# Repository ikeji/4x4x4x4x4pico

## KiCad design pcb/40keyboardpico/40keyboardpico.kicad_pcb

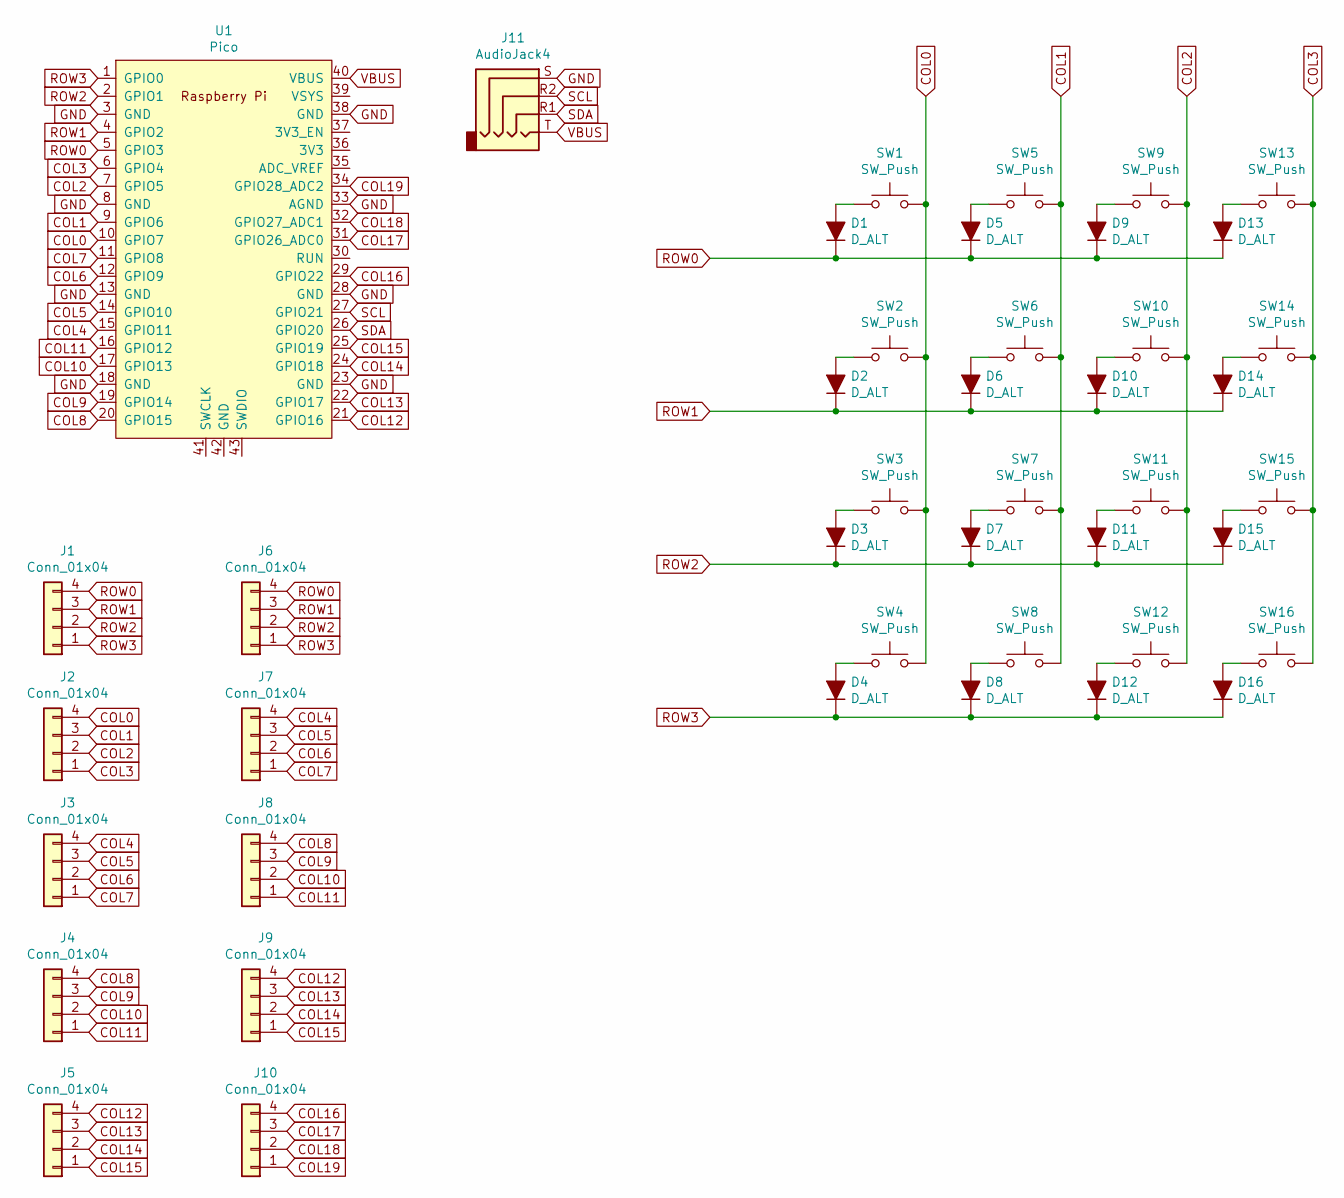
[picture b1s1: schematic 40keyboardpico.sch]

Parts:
D1, D2, D3, D4, D5, D6, D7, D8, D9, D10, D11, D12, D13, D14, D15, D16: D_ALT; D_DO-34_SOD68_P10.16mm_Horizontal
J1, J2, J3, J4, J5, J6, J7, J8, J9, J10: Conn_01x04; PinHeader_1x04_P2.54mm_Vertical
J11: AudioJack4; Jack_3.5mm_PJ320E_Horizontal
SW1, SW2, SW3, SW4, SW5, SW6, SW7, SW8, SW9, SW10, SW11, SW12, SW13, SW14, SW15, SW16: SW_Push; SW_Cherry_MX_1.00u_PCB
U1: Pico; RPi_Pico_SMD_TH

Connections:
COL0: J2.4, SW1.2, SW2.2, SW3.2, SW4.2, U1.10 (GPIO7)
COL1: J2.3, SW5.2, SW6.2, SW7.2, SW8.2, U1.9 (GPIO6)
COL2: J2.2, SW9.2, SW10.2, SW11.2, SW12.2, U1.7 (GPIO5)
COL3: J2.1, SW13.2, SW14.2, SW15.2, SW16.2, U1.6 (GPIO4)
COL4: J3.4, J7.4, U1.15 (GPIO11)
COL5: J3.3, J7.3, U1.14 (GPIO10)
COL6: J3.2, J7.2, U1.12 (GPIO9)
COL7: J3.1, J7.1, U1.11 (GPIO8)
COL8: J4.4, J8.4, U1.20 (GPIO15)
COL9: J4.3, J8.3, U1.19 (GPIO14)
COL10: J4.2, J8.2, U1.17 (GPIO13)
COL11: J4.1, J8.1, U1.16 (GPIO12)
COL12: J5.4, J9.4, U1.21 (GPIO16)
COL13: J5.3, J9.3, U1.22 (GPIO17)
COL14: J5.2, J9.2, U1.24 (GPIO18)
COL15: J5.1, J9.1, U1.25 (GPIO19)
COL16: J10.4, U1.29 (GPIO22)
COL17: J10.3, U1.31 (GPIO26_ADC0)
COL18: J10.2, U1.32 (GPIO27_ADC1)
COL19: J10.1, U1.34 (GPIO28_ADC2)
GND: J11.S, U1.3 (GND), U1.8 (GND), U1.13 (GND), U1.18 (GND), U1.23 (GND), U1.28 (GND), U1.33 (AGND), U1.38 (GND)
unnamed: D1.2 (A), SW1.1
unnamed: D2.2 (A), SW2.1
unnamed: D3.2 (A), SW3.1
unnamed: D4.2 (A), SW4.1
unnamed: D5.2 (A), SW5.1
unnamed: D6.2 (A), SW6.1
unnamed: D7.2 (A), SW7.1
unnamed: D8.2 (A), SW8.1
unnamed: D9.2 (A), SW9.1
unnamed: D10.2 (A), SW10.1
unnamed: D11.2 (A), SW11.1
unnamed: D12.2 (A), SW12.1
unnamed: D13.2 (A), SW13.1
unnamed: D14.2 (A), SW14.1
unnamed: D15.2 (A), SW15.1
unnamed: D16.2 (A), SW16.1
ROW0: D1.1 (K), D5.1 (K), D9.1 (K), D13.1 (K), J1.4, J6.4, U1.5 (GPIO3)
ROW1: D2.1 (K), D6.1 (K), D10.1 (K), D14.1 (K), J1.3, J6.3, U1.4 (GPIO2)
ROW2: D3.1 (K), D7.1 (K), D11.1 (K), D15.1 (K), J1.2, J6.2, U1.2 (GPIO1)
ROW3: D4.1 (K), D8.1 (K), D12.1 (K), D16.1 (K), J1.1, J6.1, U1.1 (GPIO0)
SCL: J11.R2, U1.27 (GPIO21)
SDA: J11.R1, U1.26 (GPIO20)
VBUS: J11.T, U1.40 (VBUS)

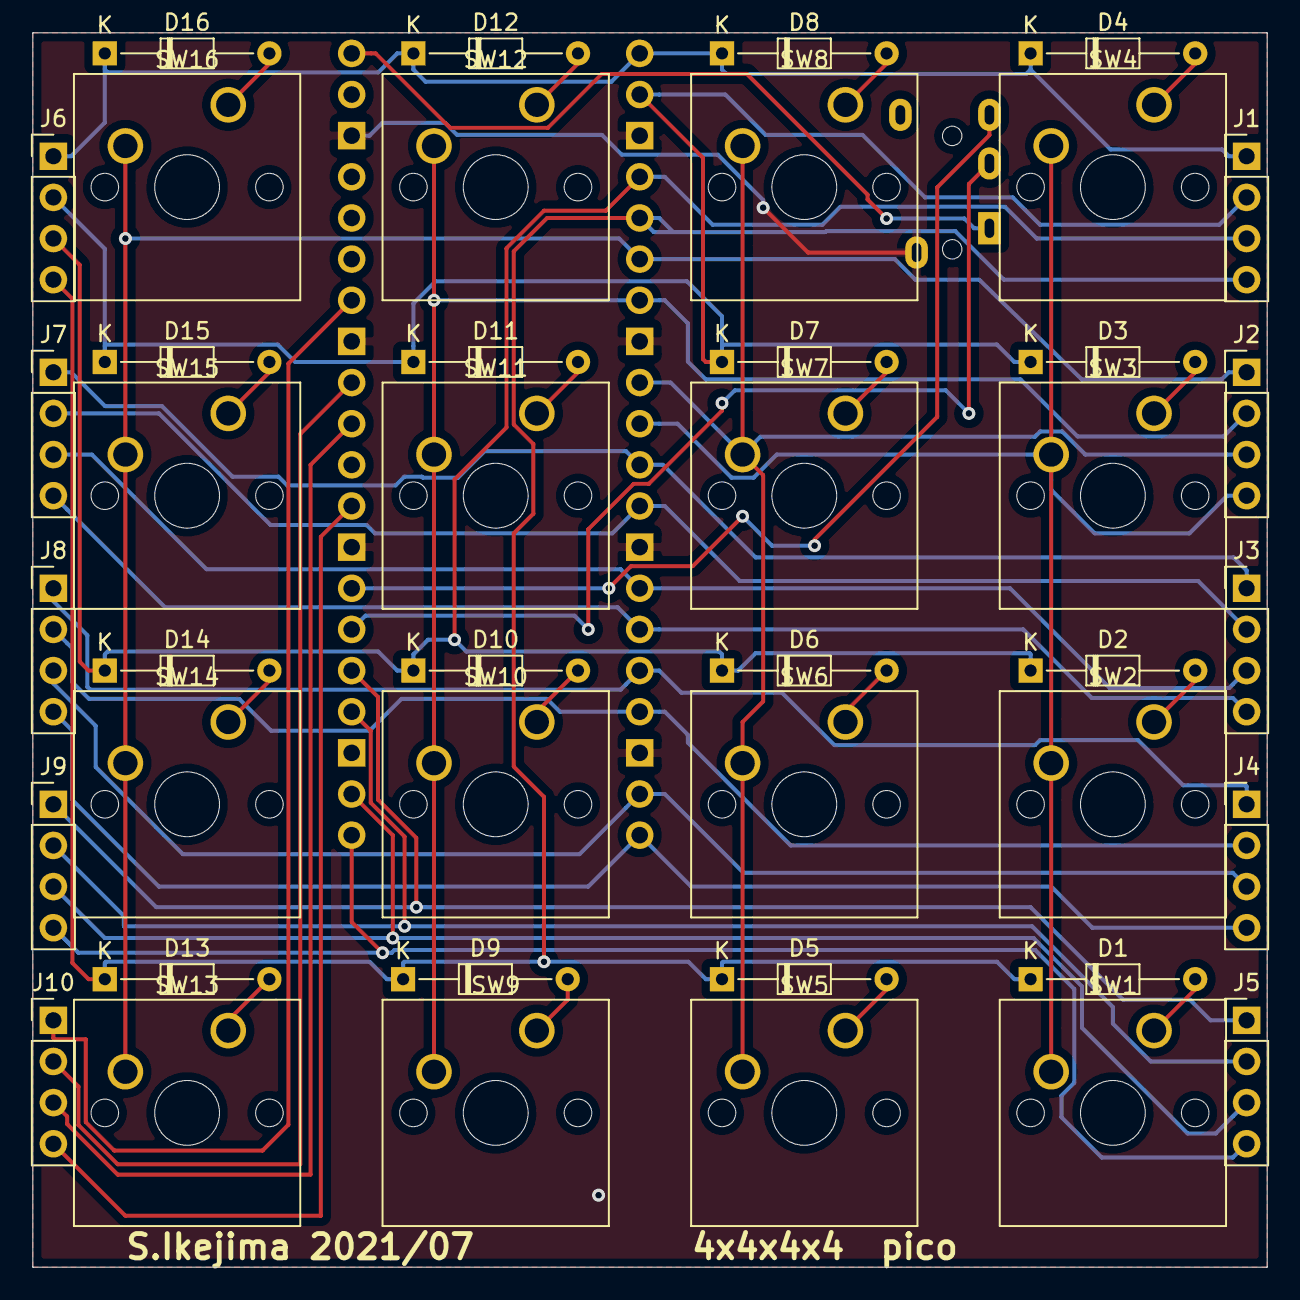
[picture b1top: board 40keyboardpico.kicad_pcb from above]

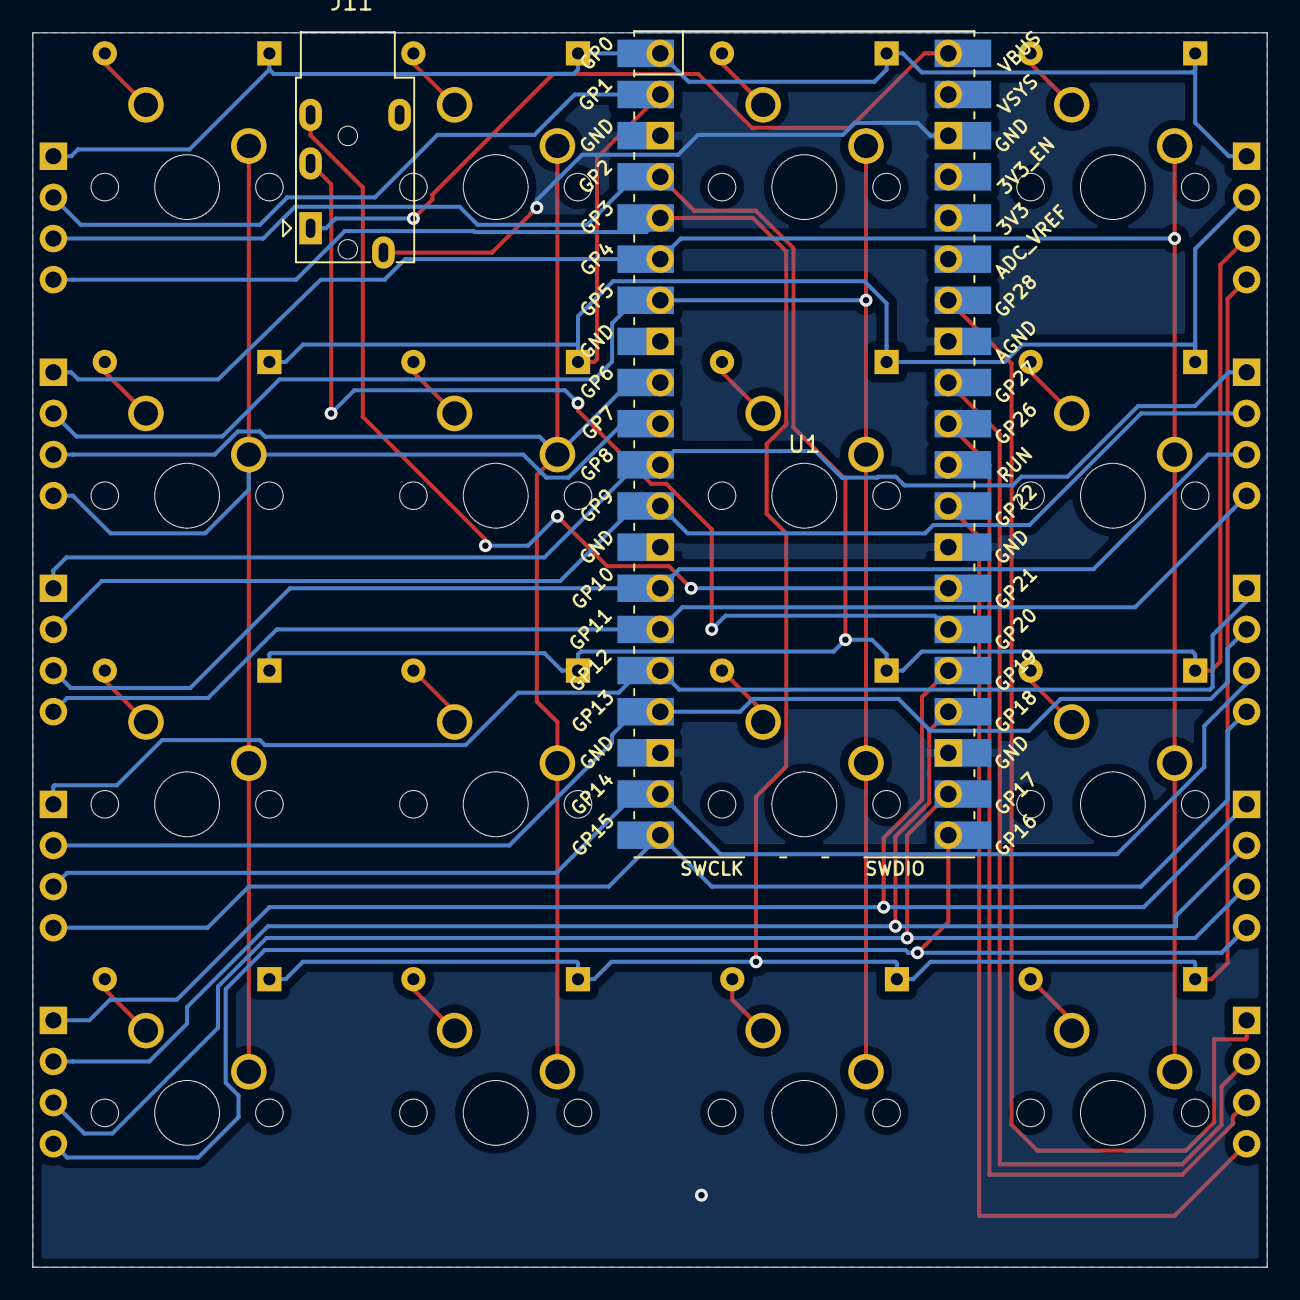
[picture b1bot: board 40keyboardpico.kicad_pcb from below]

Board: 2 copper layers, 76.2 x 76.2 mm, 44 parts (2 on the bottom side), 44 nets.

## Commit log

2021-07-28 Initial commit.
2021-07-28 Export as PDF.
2021-07-29 Add area ground.
2021-07-30 Send it to all pcb.
